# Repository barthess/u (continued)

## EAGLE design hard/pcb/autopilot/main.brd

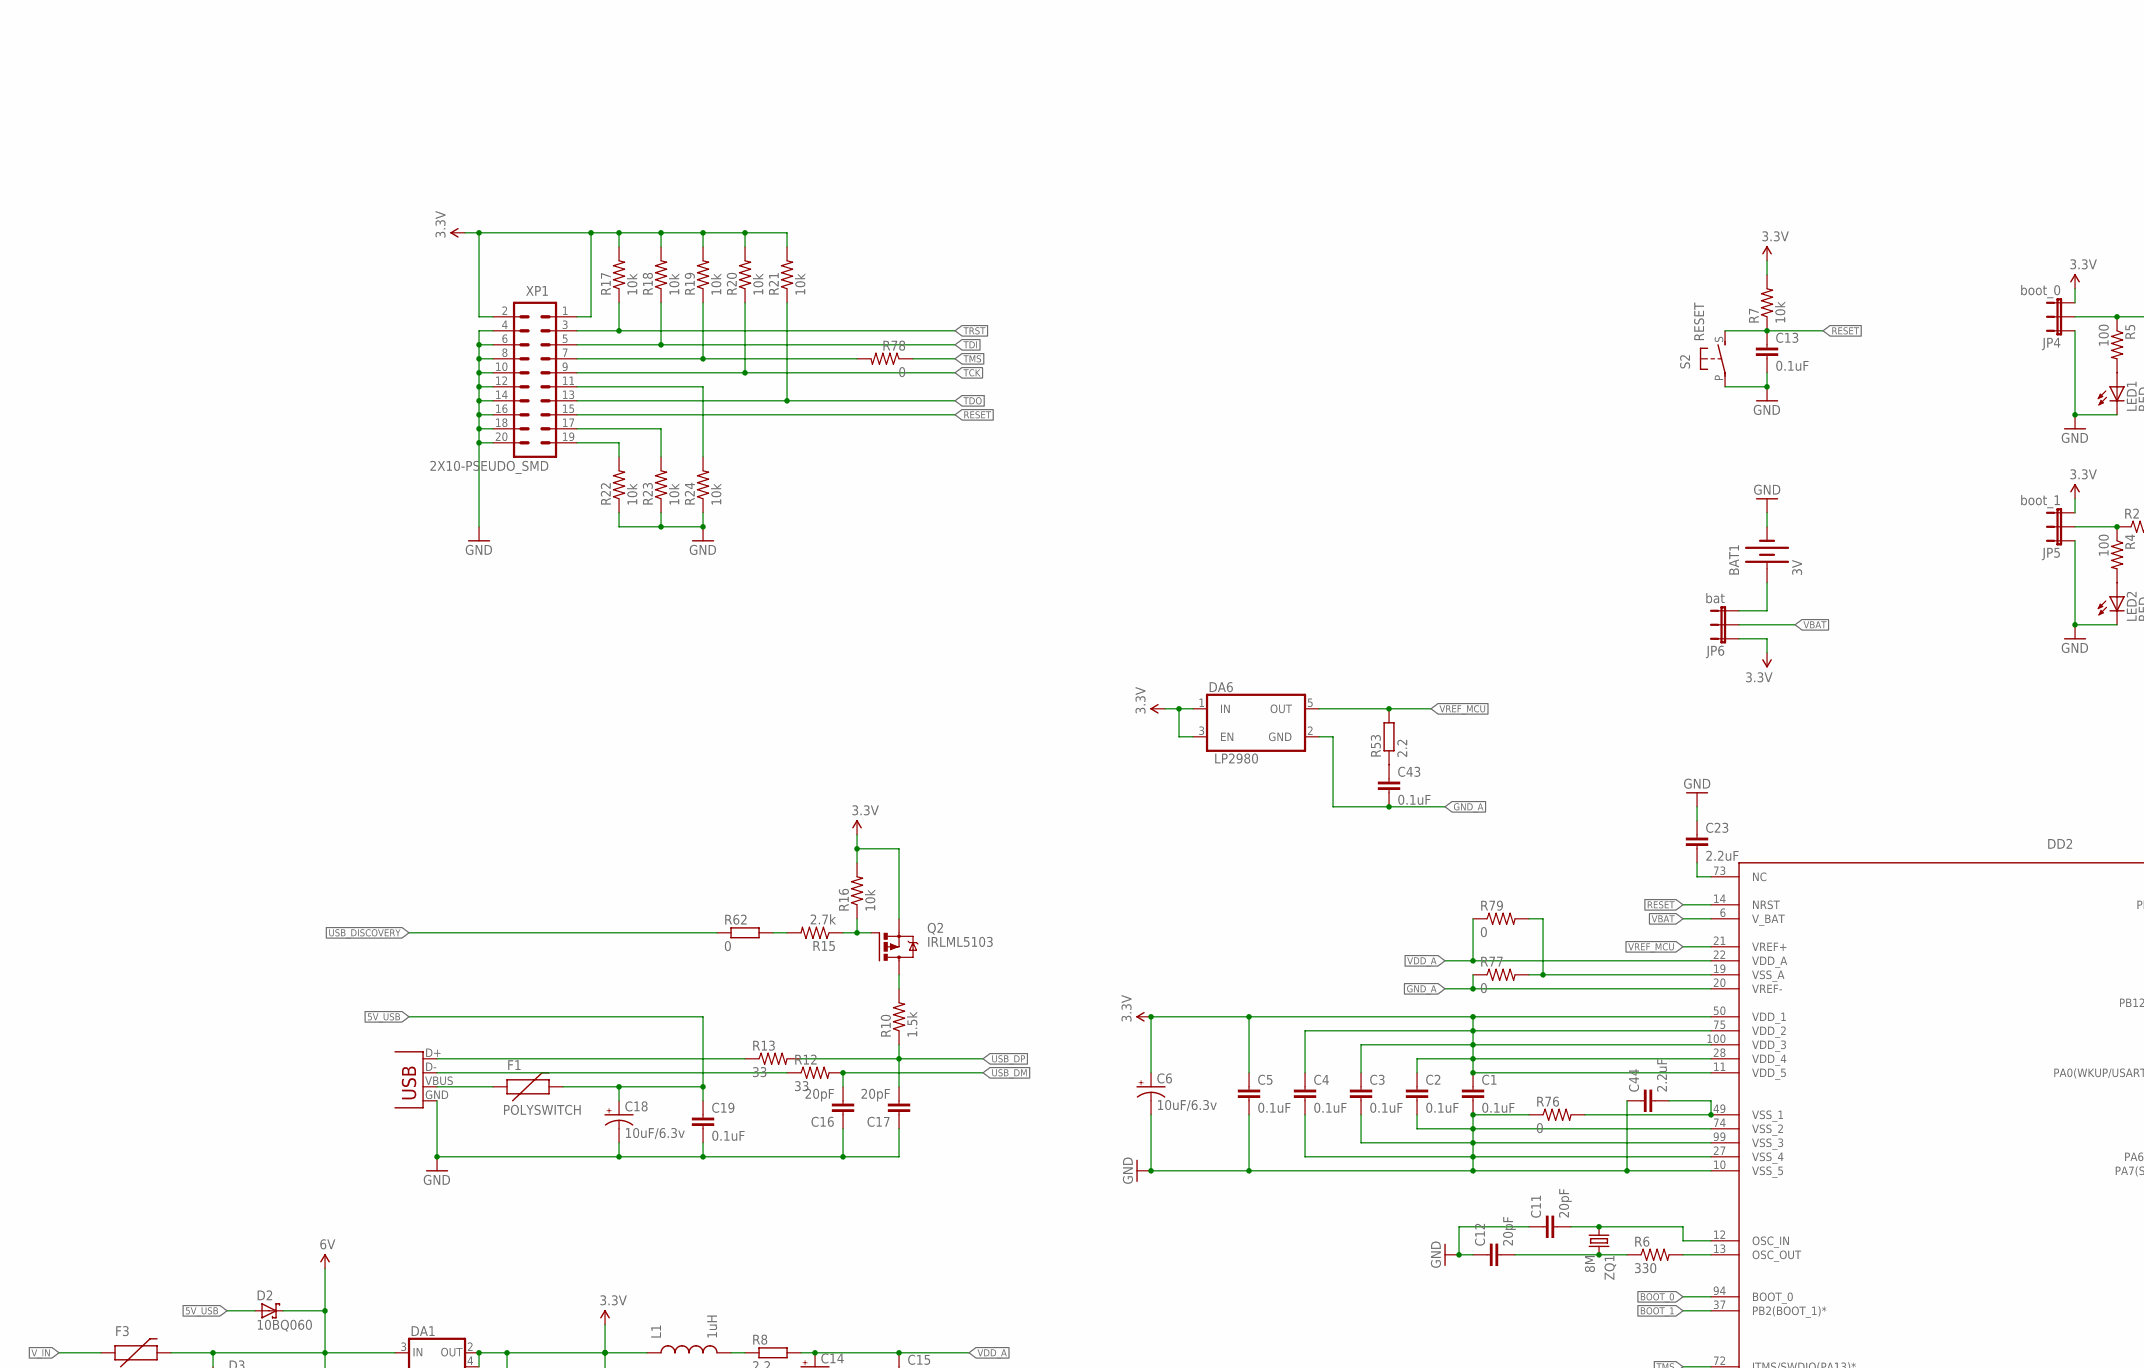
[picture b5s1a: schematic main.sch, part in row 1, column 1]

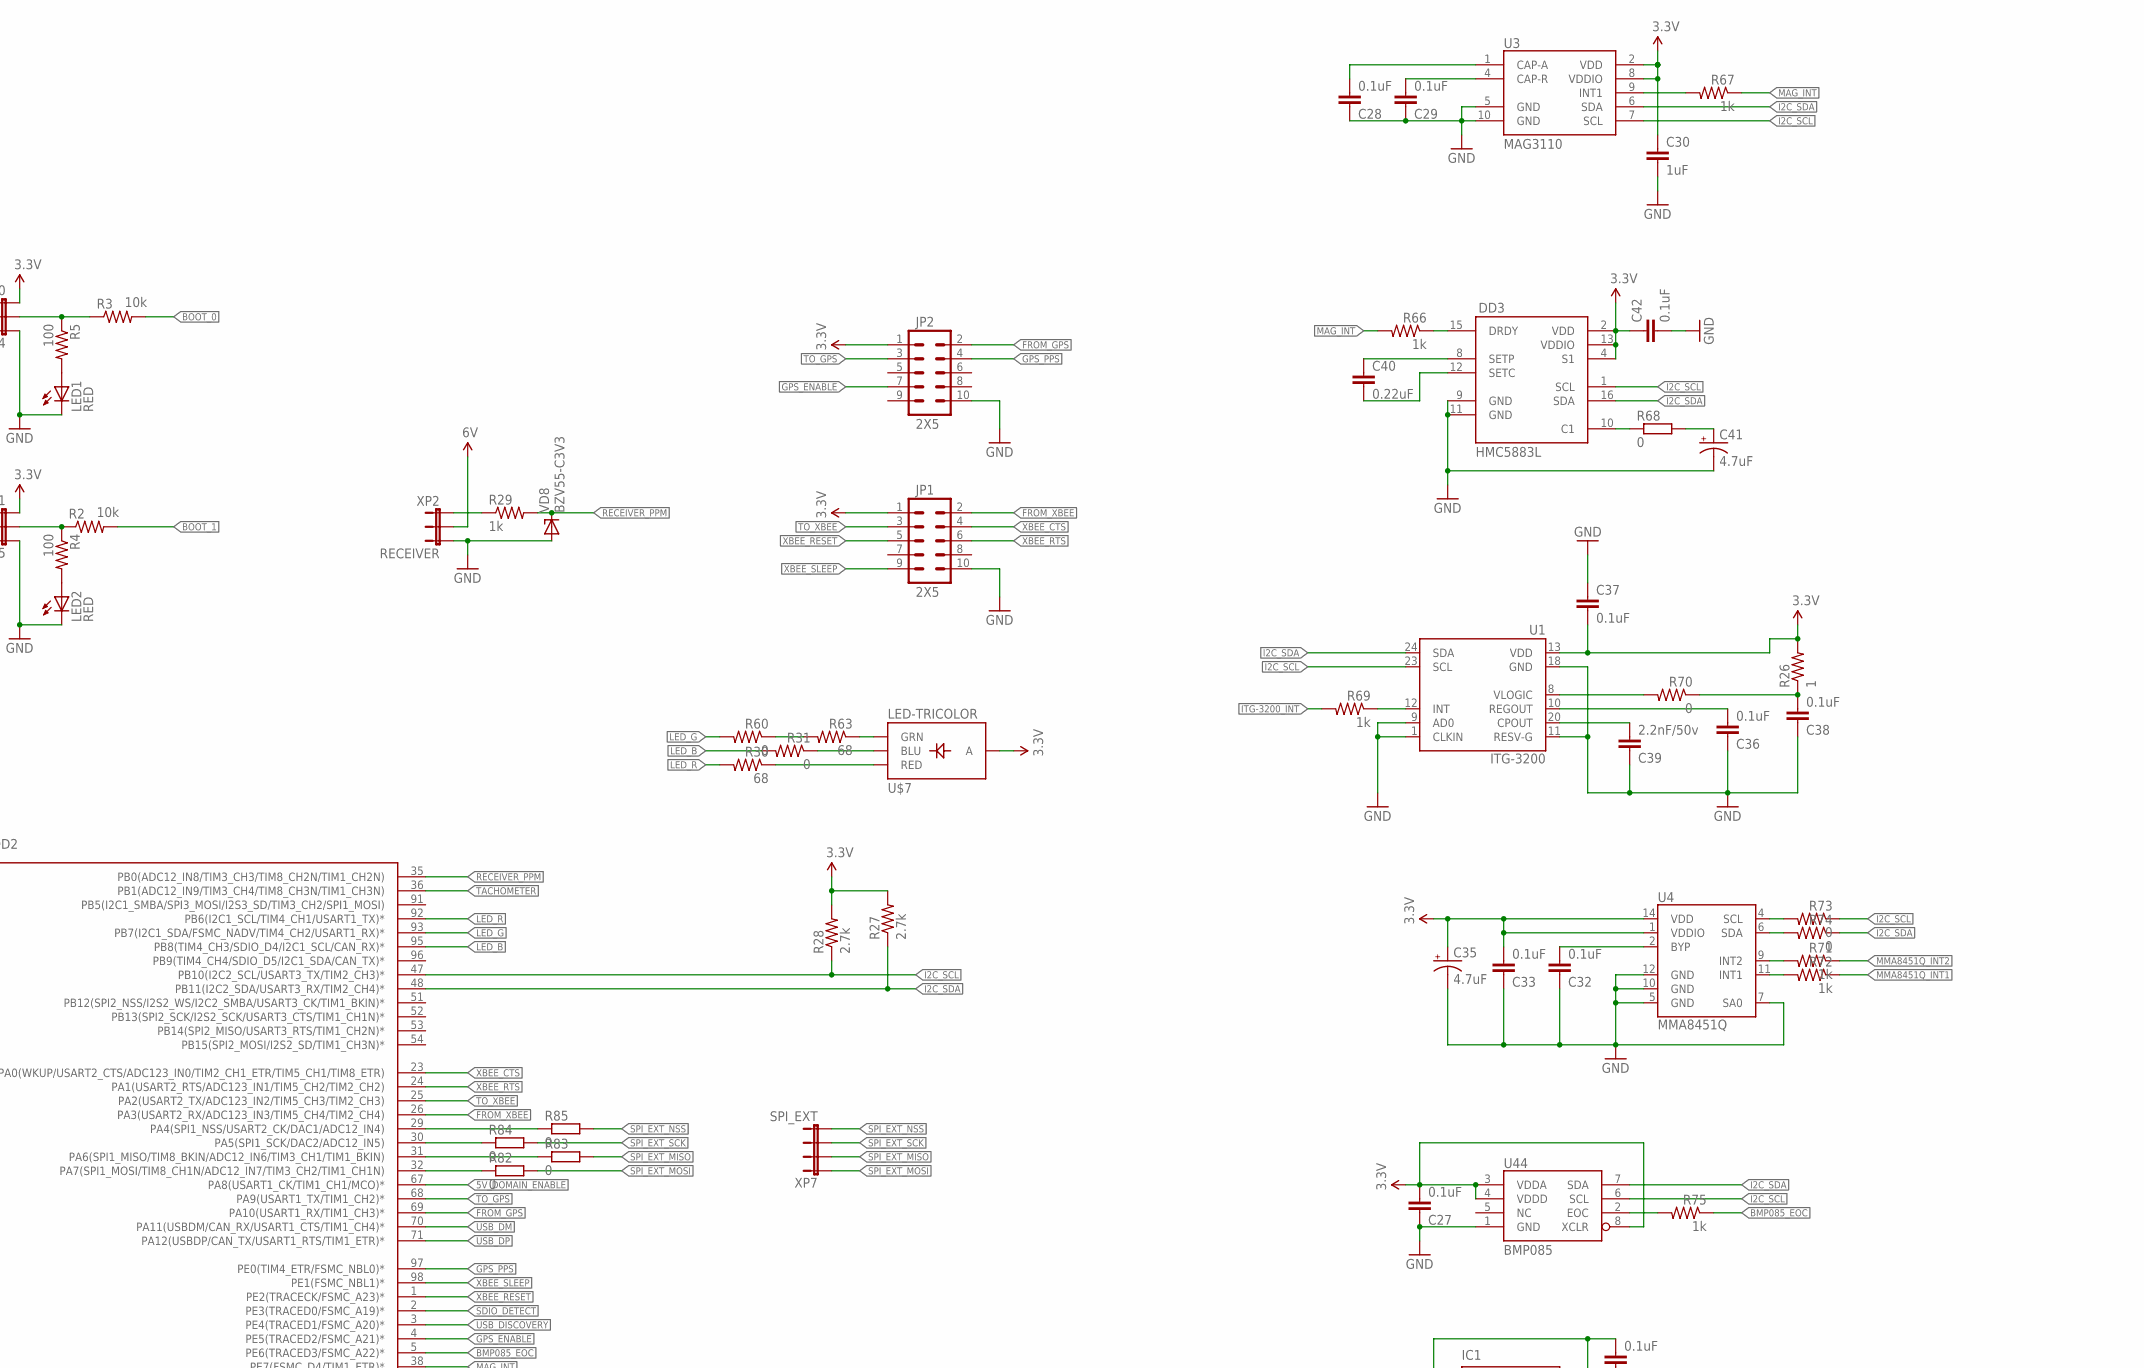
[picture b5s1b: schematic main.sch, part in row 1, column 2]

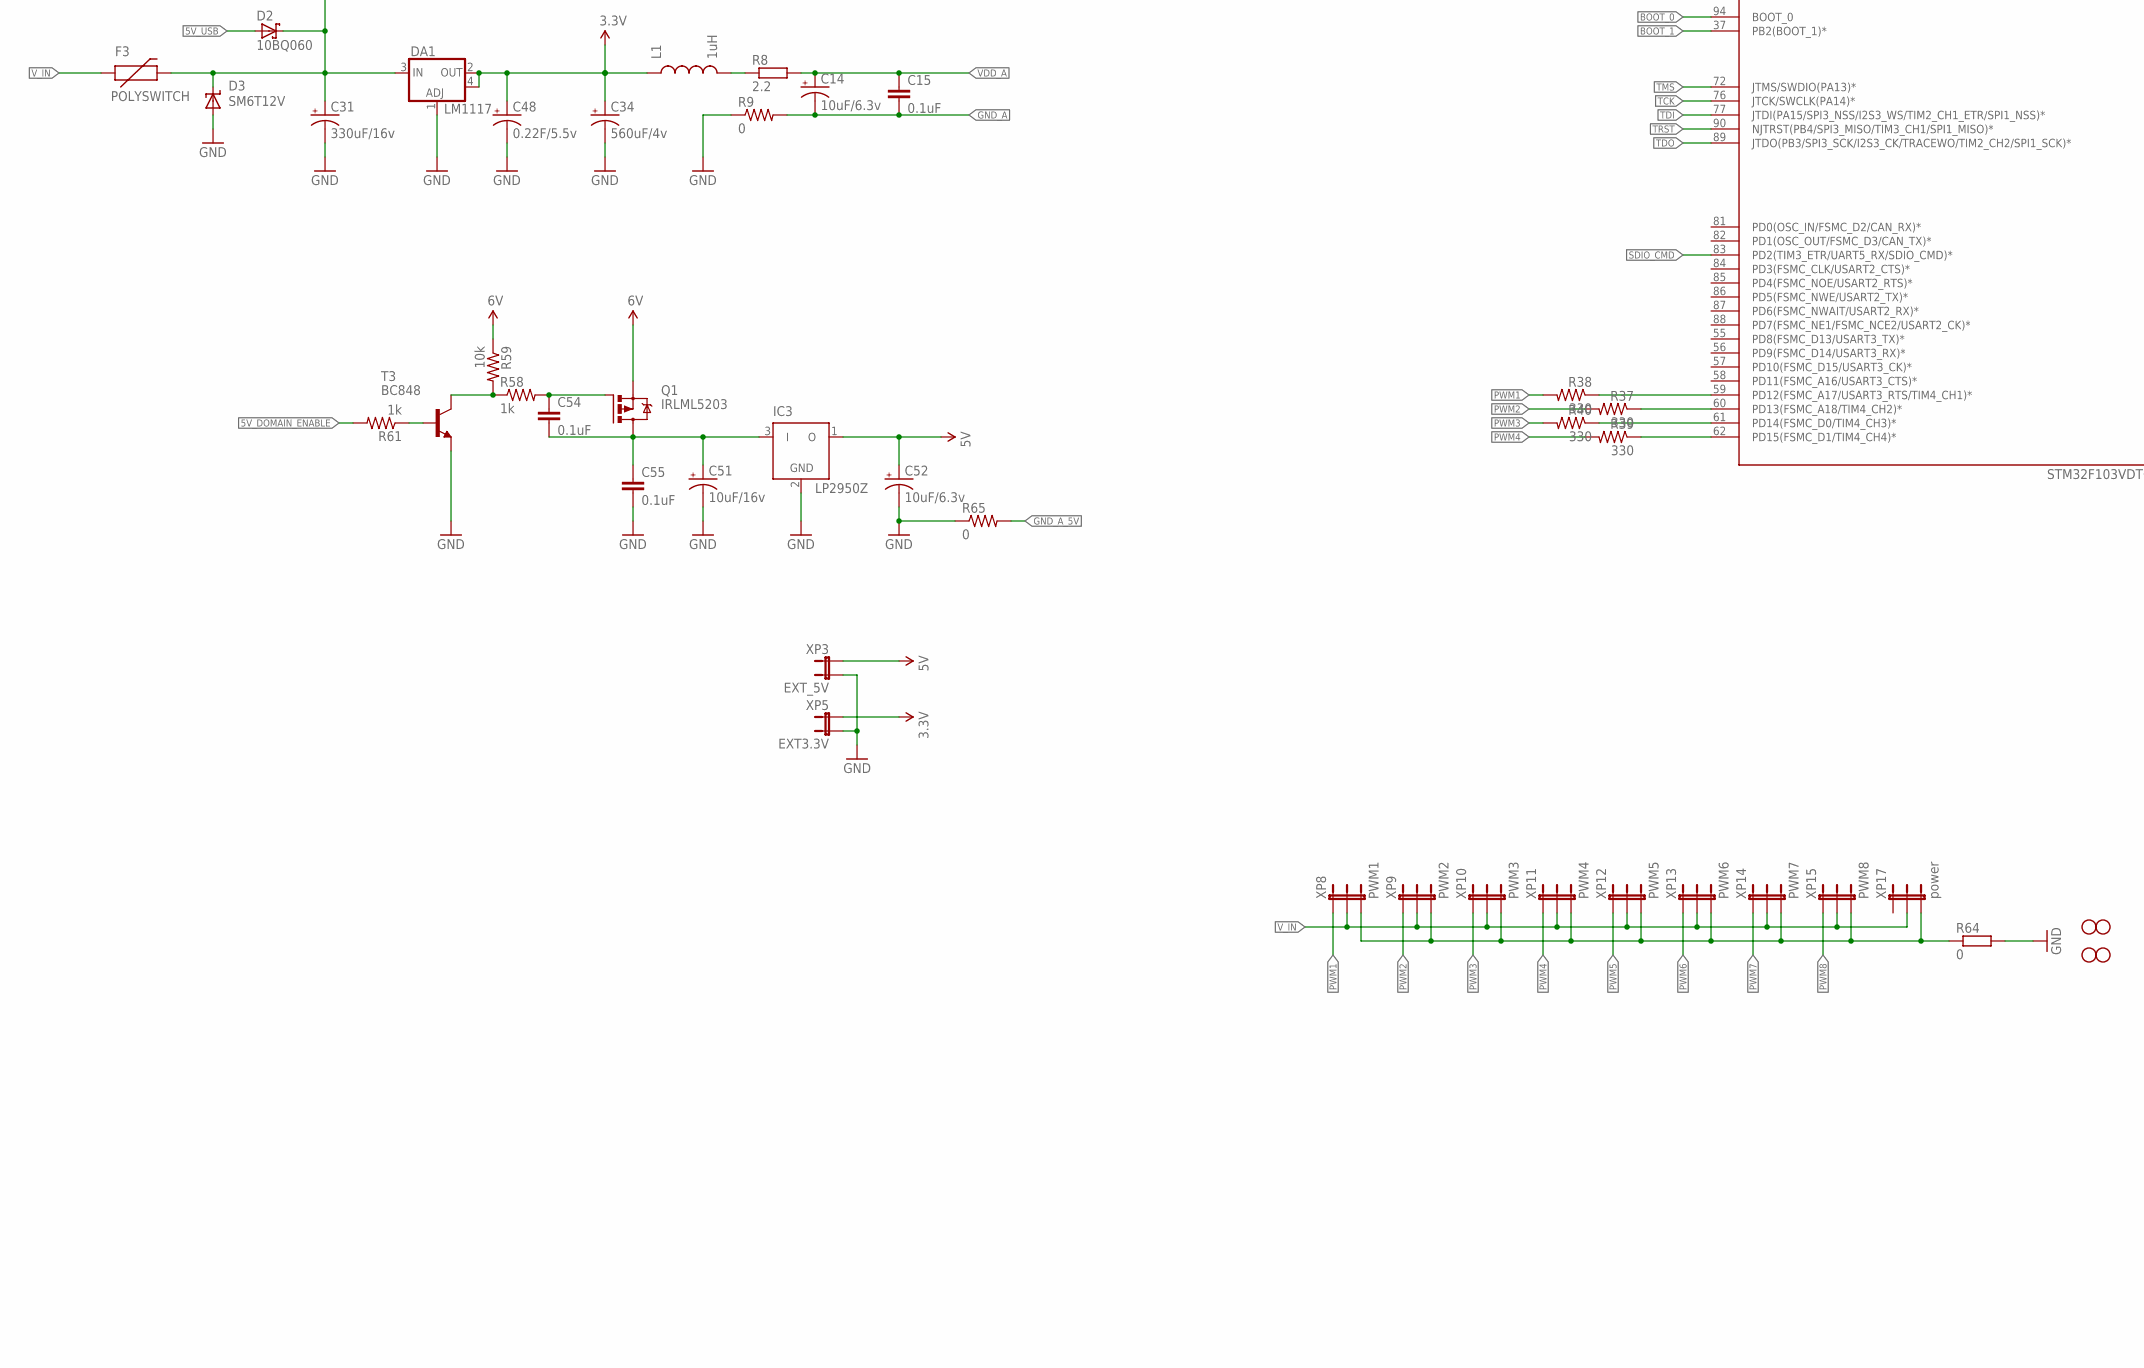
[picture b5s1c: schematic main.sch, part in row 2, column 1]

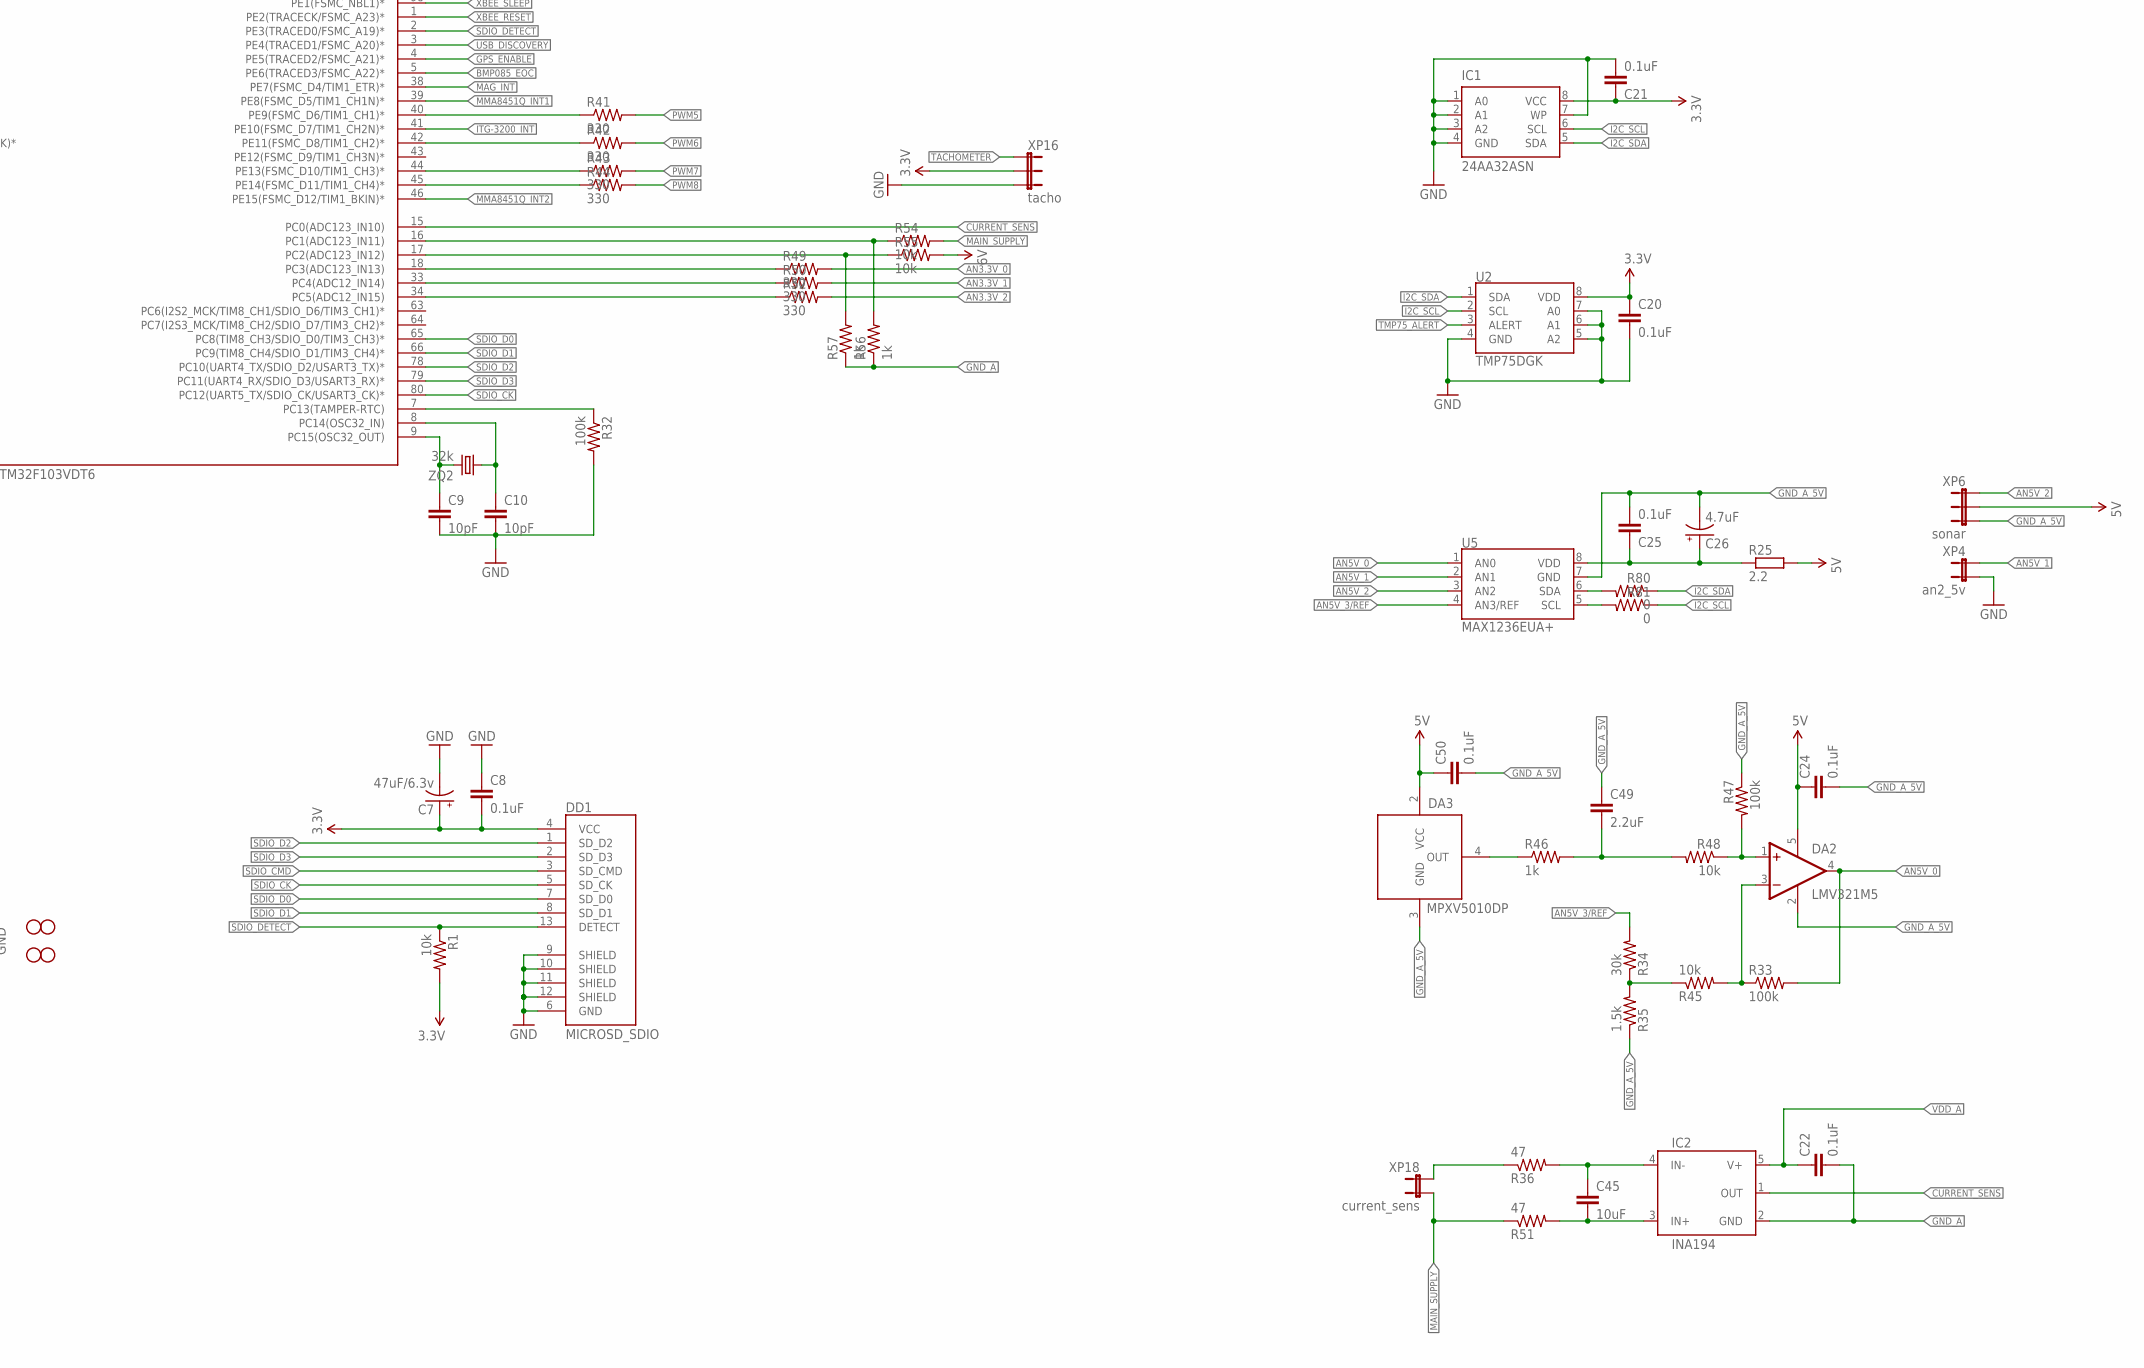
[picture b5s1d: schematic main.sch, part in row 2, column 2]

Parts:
BAT1: 3V; BATTCOM_20MM_PTH
C1, C2, C3, C4, C5, C8, C13, C15, C19, C20, C21, C22, C24, C25, C27, C28, C29, C32, C33, C36, C37, C38, C42, C43, C50, C54, C55: 0.1uF; 0805
C6, C14, C18, C52: 10uF/6.3v; EIA3216-KIT
C7: 47uF/6.3v; EIA3216-KIT
C9, C10: 10pF; 0805
C11, C12, C16, C17: 20pF; 0805
C23, C44: 2.2uF; 0805
C26, C35, C41: 4.7uF; EIA3216-KIT
C30: 1uF; 0805
C31: 330uF/16v; CPOL-RADIAL-1000UF-25V
C34: 560uF/4v; E3,5-8
C39: 2.2nF/50v; 0805
C40: 0.22uF; 0805
C45: 10uF; 1206
C48: 0.22F/5.5v; CAP-IONISTOR-5MM
C49: 2.2uF; C1206
C51: 10uF/16v; EIA3216-KIT
D2: 10BQ060; SMB
D3: SM6T12V; SMBJ
DA1: LM1117; SOT223
DA2: LMV321M5; SOT23-5
DA3: MPXV5010DP; 482
DA6: LP2980; SOT23-5
DD1: MICROSD_SDIO; MICROSD
DD2: STM32F103VDT6; TQFP100
DD3: HMC5883L; 16LPCC
F1, F3: POLYSWITCH; 1812
IC1: 24AA32ASN; SO-08
IC2: INA194; SOT23-5
IC3: LP2950Z; TO92
JP1, JP2: 2X5; 2X5-PSEUDOSMD
JP3, JP7, JP8, JP9: STAND-OFFTIGHT; STAND-OFF-TIGHT
JP4: boot_0; 1X03
JP5: boot_1; 1X03
JP6: bat; 1X03
L1: 1uH; 1210
LED1, LED2: RED; LED-0805
Q1: IRLML5203; MICRO3
Q2: IRLML5103; MICRO3; PARTNO *
R1, R2, R3, R7, R16, R17, R18, R19, R20, R21, R22, R23, R24, R45, R48, R54, R55, R59: 10k; 0805
R4, R5: 100; 0805
R6, R37, R38, R39, R40, R41, R42, R43, R44, R49, R50, R52: 330; 0805
R8, R25, R53: 2.2; R1206
R9, R31, R60, R65, R70, R73, R74, R76, R77, R78, R79, R80, R81: 0; 0805
R10, R35: 1.5k; 0805
R12, R13: 33; 0805
R15, R27, R28: 2.7k; 0805
R26: 1; 0805
R29, R46, R56, R57, R58, R61, R66, R67, R69, R71, R72, R75: 1k; 0805
R30, R63: 68; 0805
R32, R33, R47: 100k; 0805
R34: 30k; 0805
R36, R51: 47; 0805
R62, R64, R68, R82, R83, R84, R85: 0; R1206
S2: RESET; BUTTON_6X3.5
T3: BC848; SOT23
U1: ITG-3200; QFN-24
U2: TMP75DGK; MSOP8
U3: MAG3110; DFN-10
U4: MMA8451Q; QFN-16_0.5MM
U5: MAX1236EUA+; MSOP8
U44: BMP085
U$7: LED-TRICOLOR; LED-TRICOLOR-SMD
VD8: BZV55-C3V3; SOD80C
X1: USB-SMD-NS; USB-MINIB-NOSTOP
XP1: 2X10-PSEUDO_SMD; 2X10-PSEUDOSMD
XP2: RECEIVER; 1X03
XP3: EXT_5V; 1X02
XP4: an2_5v; 1X02
XP5: EXT3.3V; 1X02
XP6: sonar; 1X03
XP7: SPI_EXT; 1X4-PSEUDOSMD
XP8: PWM1; 1X03
XP9: PWM2; 1X03
XP10: PWM3; 1X03
XP11: PWM4; 1X03
XP12: PWM5; 1X03
XP13: PWM6; 1X03
XP14: PWM7; 1X03
XP15: PWM8; 1X03
XP16: tacho; 1X03
XP17: power; 1X03
XP18: current_sens; 1X02
ZQ1: 8M; HC49U-V
ZQ2: 32k; TC38H

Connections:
3.3V: C1.1, C2.1, C3.1, C4.1, C5.1, C6.A (+), C7.A (+), C8.2, C20.1, C21.1, C27.2, C30.1, C33.2, C34.+, C35.A (+), C37.2, C42.1, C48.1 (+), DA1.2 (OUT), DA1.4 (OUT), DA6.1 (IN), DA6.3 (EN), DD1.4 (VCC), DD2.11 (VDD_5), DD2.28 (VDD_4), DD2.50 (VDD_1), DD2.75 (VDD_2), DD2.100 (VDD_3), DD3.2 (VDD), DD3.4 (S1), DD3.13 (VDDIO), IC1.8 (VCC), JP1.1, JP2.1, JP4.3, JP5.3, JP6.1, L1.1, Q2.2 (S), R1.2, R7.2, R16.2, R17.2, R18.2, R19.2, R20.2, R21.2, R26.2, R27.2, R28.2, U1.13 (VDD), U2.8 (VDD), U3.2 (VDD), U3.8 (VDDIO), U4.1 (VDDIO), U4.14 (VDD), U44.3 (VDDA), U44.4 (VDDD), U44.8 (XCLR), U$7.A, XP1.1, XP1.2, XP5.1, XP16.2
5V: C24.1, C50.1, C52.A (+), DA2.5 (V+), DA3.2 (VCC), IC3.1 (O), R25.2, XP3.1, XP6.2
5V_DOMAIN_ENABLE: DD2.67 (PA8(USART1_CK/TIM1_CH1/MCO)*), R61.2
5V_USB: C18.A (+), C19.1, D2.A, F1.2
6V: C31.1 (+), D2.C, D3.C, DA1.3 (IN), F3.2, Q1.2 (S), R55.2, R59.1, XP2.2
AN3.3V_0: R49.2
AN3.3V_1: R50.2
AN3.3V_2: R52.2
AN5V_0: DA2.4 (OUT), R33.2, U5.1 (AN0)
AN5V_1: U5.2 (AN1), XP4.1
AN5V_2: U5.3 (AN2), XP6.1
AN5V_3/REF: R34.2, U5.4 (AN3/REF)
BMP085_EOC: DD2.5 (PE6(TRACED3/FSMC_A22)*), R75.1
BOOT_0: DD2.94 (BOOT_0), R3.2
BOOT_1: DD2.37 (PB2(BOOT_1)*), R2.2
CURRENT_SENS: DD2.15 (PC0(ADC123_IN10)), IC2.1 (OUT)
FROM_GPS: DD2.69 (PA10(USART1_RX/TIM1_CH3)*), JP2.2
FROM_XBEE: DD2.26 (PA3(USART2_RX/ADC123_IN3/TIM5_CH4/TIM2_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), JP1.2
GND: BAT1.2 (-), C1.2, C2.2, C3.2, C4.2, C5.2, C6.C (-), C7.C (-), C8.1, C9.2, C10.2, C11.1, C12.1, C13.2, C16.1, C17.1, C18.C (-), C19.2, C20.2, C21.2, C23.1, C27.1, C28.1, C29.1, C30.2, C31.2 (-), C32.1, C33.1, C34.-, C35.C (-), C36.1, C37.1, C38.1, C39.1, C41.C (-), C42.2, C44.1, C48.2 (-), C51.C (-), C52.C (-), C55.2, D3.A, DA1.1 (ADJ), DD1.6 (GND), DD1.9 (SHIELD), DD1.10 (SHIELD), DD1.11 (SHIELD), DD1.12 (SHIELD), DD2.10 (VSS_5), DD2.27 (VSS_4), DD2.74 (VSS_2), DD2.99 (VSS_3), DD3.9 (GND), DD3.11 (GND), IC1.1 (A0), IC1.2 (A1), IC1.3 (A2), IC1.4 (GND), IC1.7 (WP), IC3.2 (GND), JP1.10, JP2.10, JP4.1, JP5.1, LED1.C, LED2.C, R9.1, R22.1, R23.1, R24.1, R32.2, R64.2, R65.1, R76.1, S2.P, T3.2 (E), U1.1 (CLKIN), U1.9 (AD0), U1.11 (RESV-G), U1.18 (GND), U2.4 (GND), U2.5 (A2), U2.6 (A1), U2.7 (A0), U3.5 (GND), U3.10 (GND), U4.5 (GND), U4.7 (SA0), U4.10 (GND), U4.12 (GND), U44.1 (GND), VD8.A, X1.GND, XP1.4, XP1.6, XP1.8, XP1.10, XP1.12, XP1.14, XP1.16, XP1.18, XP1.20, XP2.3, XP3.2, XP4.2, XP5.2, XP16.3
GND_A: C14.C (-), C15.2, C22.2, C43.2, DA6.2 (GND), DD2.20 (VREF-), IC2.2 (GND), R9.2, R56.1, R57.1, R77.1
GND_A_5V: C24.2, C25.2, C26.C (-), C49.1, C50.2, DA2.2 (V-), DA3.3 (GND), R35.1, R47.1, R65.2, U5.7 (GND), XP6.3
GPS_ENABLE: DD2.4 (PE5(TRACED2/FSMC_A21)*), JP2.7
GPS_PPS: DD2.97 (PE0(TIM4_ETR/FSMC_NBL0)*), JP2.4
I2C_SCL: DD2.47 (PB10(I2C2_SCL/USART3_TX/TIM2_CH3)*), DD3.1 (SCL), IC1.6 (SCL), R28.1, R73.1, R81.1, U1.23 (SCL), U2.2 (SCL), U3.7 (SCL), U44.6 (SCL)
I2C_SDA: DD2.48 (PB11(I2C2_SDA/USART3_RX/TIM2_CH4)*), DD3.16 (SDA), IC1.5 (SDA), R27.1, R74.1, R80.1, U1.24 (SDA), U2.1 (SDA), U3.6 (SDA), U44.7 (SDA)
ITG-3200_INT: DD2.41 (PE10(FSMC_D7/TIM1_CH2N)*), R69.2
LED_B: DD2.95 (PB8(TIM4_CH3/SDIO_D4/I2C1_SCL/CAN_RX)*), R31.2
LED_G: DD2.93 (PB7(I2C1_SDA/FSMC_NADV/TIM4_CH2/USART1_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), R60.2
LED_R: DD2.92 (PB6(I2C1_SCL/TIM4_CH1/USART1_TX)*), R30.2
MAG_INT: DD2.38 (PE7(FSMC_D4/TIM1_ETR)*), R66.2, R67.1
MAIN_SUPPLY: R51.1, R54.2, XP18.2
MMA8451Q_INT1: DD2.39 (PE8(FSMC_D5/TIM1_CH1N)*), R72.1
MMA8451Q_INT2: DD2.46 (PE15(FSMC_D12/TIM1_BKIN)*), R71.1
unnamed: C9.1, DD2.9 (PC15(OSC32_OUT)), ZQ2.2
unnamed: LED2.A, R4.2
unnamed: JP5.2, R2.1, R4.1
unnamed: LED1.A, R5.2
unnamed: JP4.2, R3.1, R5.1
unnamed: C10.1, DD2.8 (PC14(OSC32_IN)), ZQ2.1
unnamed: DD2.13 (OSC_OUT), R6.2
unnamed: C12.2, R6.1, ZQ1.2
unnamed: C11.2, DD2.12 (OSC_IN), ZQ1.1
unnamed: R12.1, X1.D-
unnamed: BAT1.1 (+), JP6.3
unnamed: L1.2, R8.1
unnamed: R13.1, X1.D+
unnamed: Q2.3 (D), R10.2
unnamed: Q2.1 (G), R15.1, R16.1
unnamed: R22.2, XP1.19
unnamed: R23.2, XP1.17
unnamed: R24.2, XP1.11
unnamed: C45.1, IC2.4 (IN-), R36.2
unnamed: C25.1, C26.A (+), R25.1, U5.8 (VDD)
unnamed: C32.2, U4.2 (BYP)
unnamed: C36.2, U1.10 (REGOUT)
unnamed: C29.2, U3.4 (CAP-R)
unnamed: C38.2, R26.1, R70.1
unnamed: C28.2, U3.1 (CAP-A)
unnamed: C40.1, DD3.8 (SETP)
unnamed: C40.2, DD3.12 (SETC)
unnamed: F1.1, X1.VBUS
unnamed: C39.2, U1.20 (CPOUT)
unnamed: C41.A (+), R68.2
unnamed: R29.1, XP2.1
unnamed: R63.1, U$7.G (GRN)
unnamed: DD2.7 (PC13(TAMPER-RTC)), R32.1
unnamed: C49.2, R46.2, R48.2
unnamed: DD2.32 (PA7(SPI1_MOSI/TIM8_CH1N/ADC12_IN7/TIM3_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), R82.1
unnamed: C45.2, IC2.3 (IN+), R51.2
unnamed: C43.1, R53.1
unnamed: R36.1, XP18.1
unnamed: DD2.62 (PD15(FSMC_D1/TIM4_CH4)*), R39.1
unnamed: DD2.61 (PD14(FSMC_D0/TIM4_CH3)*), R40.1
unnamed: DD2.60 (PD13(FSMC_A18/TIM4_CH2)*), R37.1
unnamed: DD2.59 (PD12(FSMC_A17/USART3_RTS/TIM4_CH1)*), R38.1
unnamed: DA3.4 (OUT), R46.1
unnamed: DD2.34 (PC5(ADC12_IN15)), R52.1
unnamed: DA2.3 (-IN), R33.1, R45.2
unnamed: DA2.1 (+IN), R47.2, R48.1
unnamed: R34.1, R35.2, R45.1
unnamed: DD2.33 (PC4(ADC12_IN14)), R50.1
unnamed: DD2.18 (PC3(ADC123_IN13)), R49.1
unnamed: DD2.31 (PA6(SPI1_MISO/TIM8_BKIN/ADC12_IN6/TIM3_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), R83.1
unnamed: DD2.16 (PC1(ADC123_IN11)), R54.1, R56.2
unnamed: C54.1, Q1.1 (G), R58.2
unnamed: DD2.17 (PC2(ADC123_IN12)), R55.1, R57.2
unnamed: C51.A (+), C54.2, C55.1, IC3.3 (I), Q1.3 (D)
unnamed: R31.1, U$7.B (BLU)
unnamed: R30.1, U$7.R (RED)
unnamed: DD2.30 (PA5(SPI1_SCK/DAC2/ADC12_IN5)), R84.1
unnamed: R61.1, T3.1 (B)
unnamed: DD2.29 (PA4(SPI1_NSS/USART2_CK/DAC1/ADC12_IN4)), R85.1
unnamed: DD2.45 (PE14(FSMC_D11/TIM1_CH4)*), R44.1
unnamed: DD2.44 (PE13(FSMC_D10/TIM1_CH3)*), R43.1
unnamed: DD2.42 (PE11(FSMC_D8/TIM1_CH2)*), R42.1
unnamed: DD2.40 (PE9(FSMC_D6/TIM1_CH1)*), R41.1
unnamed: R67.2, U3.9 (INT1)
unnamed: DD3.15 (DRDY), R66.1
unnamed: DD3.10 (C1), R68.1
unnamed: R69.1, U1.12 (INT)
unnamed: R70.2, U1.8 (VLOGIC)
unnamed: R71.2, U4.9 (INT2)
unnamed: R72.2, U4.11 (INT1)
unnamed: R74.2, U4.6 (SDA)
unnamed: R73.2, U4.4 (SCL)
unnamed: R75.2, U44.2 (EOC)
unnamed: R15.2, R62.2
unnamed: R60.1, R63.2
unnamed: R19.1, R78.2, XP1.7
unnamed: R64.1, XP8.3, XP9.3, XP10.3, XP11.3, XP12.3, XP13.3, XP14.3, XP15.3, XP17.3
unnamed: R80.2, U5.6 (SDA)
unnamed: R81.2, U5.5 (SCL)
unnamed: C23.2, DD2.73 (NC)
unnamed: C44.2, DD2.49 (VSS_1), R76.2
unnamed: DD2.19 (VSS_A), R77.2, R79.2
NET$1: R58.1, R59.2, T3.3 (C)
PWM1: R38.2, XP8.1
PWM2: R37.2, XP9.1
PWM3: R40.2, XP10.1
PWM4: R39.2, XP11.1
PWM5: R41.2, XP12.1
PWM6: R42.2, XP13.1
PWM7: R43.2, XP14.1
PWM8: R44.2, XP15.1
RECEIVER_PPM: DD2.35 (PB0(ADC12_IN8/TIM3_CH3/TIM8_CH2N/TIM1_C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), R29.2, VD8.C
RESET: C13.1, DD2.14 (NRST), R7.1, S2.S, XP1.15
SDIO_CK: DD1.5 (SD_CK), DD2.80 (PC12(UART5_TX/SDIO_CK/USART3_CK)*)
SDIO_CMD: DD1.3 (SD_CMD), DD2.83 (PD2(TIM3_ETR/UART5_RX/SDIO_CMD)*)
SDIO_D0: DD1.7 (SD_D0), DD2.65 (PC8(TIM8_CH3/SDIO_D0/TIM3_CH3)*)
SDIO_D1: DD1.8 (SD_D1), DD2.66 (PC9(TIM8_CH4/SDIO_D1/TIM3_CH4)*)
SDIO_D2: DD1.1 (SD_D2), DD2.78 (PC10(UART4_TX/SDIO_D2/USART3_TX)*)
SDIO_D3: DD1.2 (SD_D3), DD2.79 (PC11(UART4_RX/SDIO_D3/USART3_RX)*)
SDIO_DETECT: DD1.13 (DETECT), DD2.2 (PE3(TRACED0/FSMC_A19)*), R1.1
SPI_EXT_MISO: R83.2, XP7.2
SPI_EXT_MOSI: R82.2, XP7.1
SPI_EXT_NSS: R85.2, XP7.4
SPI_EXT_SCK: R84.2, XP7.3
TACHOMETER: DD2.36 (PB1(ADC12_IN9/TIM3_CH4/TIM8_CH3N/TIM1_C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), XP16.1
TCK: DD2.76 (JTCK/SWCLK(PA14)*), R20.1, XP1.9
TDI: DD2.77 (JTDI(PA15/SPI3_NSS/I2S3_WS/TIM2_CH1_ETR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), R18.1, XP1.5
TDO: DD2.89 (JTDO(PB3/SPI3_SCK/I2S3_CK/TRACEWO/TIM2_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), R21.1, XP1.13
TMP75_ALERT: U2.3 (ALERT)
TMS: DD2.72 (JTMS/SWDIO(PA13)*), R78.1
TO_GPS: DD2.68 (PA9(USART1_TX/TIM1_CH2)*), JP2.3
TO_XBEE: DD2.25 (PA2(USART2_TX/ADC123_IN2/TIM5_CH3/TIM2_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), JP1.3
TRST: DD2.90 (NJTRST(PB4/SPI3_MISO/TIM3_CH1/SPI1_MISO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), R17.1, XP1.3
USB_DISCOVERY: DD2.3 (PE4(TRACED1/FSMC_A20)*), R62.1
USB_DM: C16.2, DD2.70 (PA11(USBDM/CAN_RX/USART1_CTS/TIM1_CH4)*), R12.2
USB_DP: C17.2, DD2.71 (PA12(USBDP/CAN_TX/USART1_RTS/TIM1_ETR)*), R10.1, R13.2
VBAT: DD2.6 (V_BAT), JP6.2
VDD_A: C14.A (+), C15.1, C22.1, DD2.22 (VDD_A), IC2.5 (V+), R8.2, R79.1
VREF_MCU: DA6.5 (OUT), DD2.21 (VREF+), R53.2
V_IN: F3.1, XP8.2, XP9.2, XP10.2, XP11.2, XP12.2, XP13.2, XP14.2, XP15.2, XP17.2
XBEE_CTS: DD2.23 (PA0(WKUP/USART2_CTS/ADC123_IN0/TIM2_CH1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), JP1.4
XBEE_RESET: DD2.1 (PE2(TRACECK/FSMC_A23)*), JP1.5
XBEE_RTS: DD2.24 (PA1(USART2_RTS/ADC123_IN1/TIM5_CH2/TIM2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), JP1.6
XBEE_SLEEP: DD2.98 (PE1(FSMC_NBL1)*), JP1.9

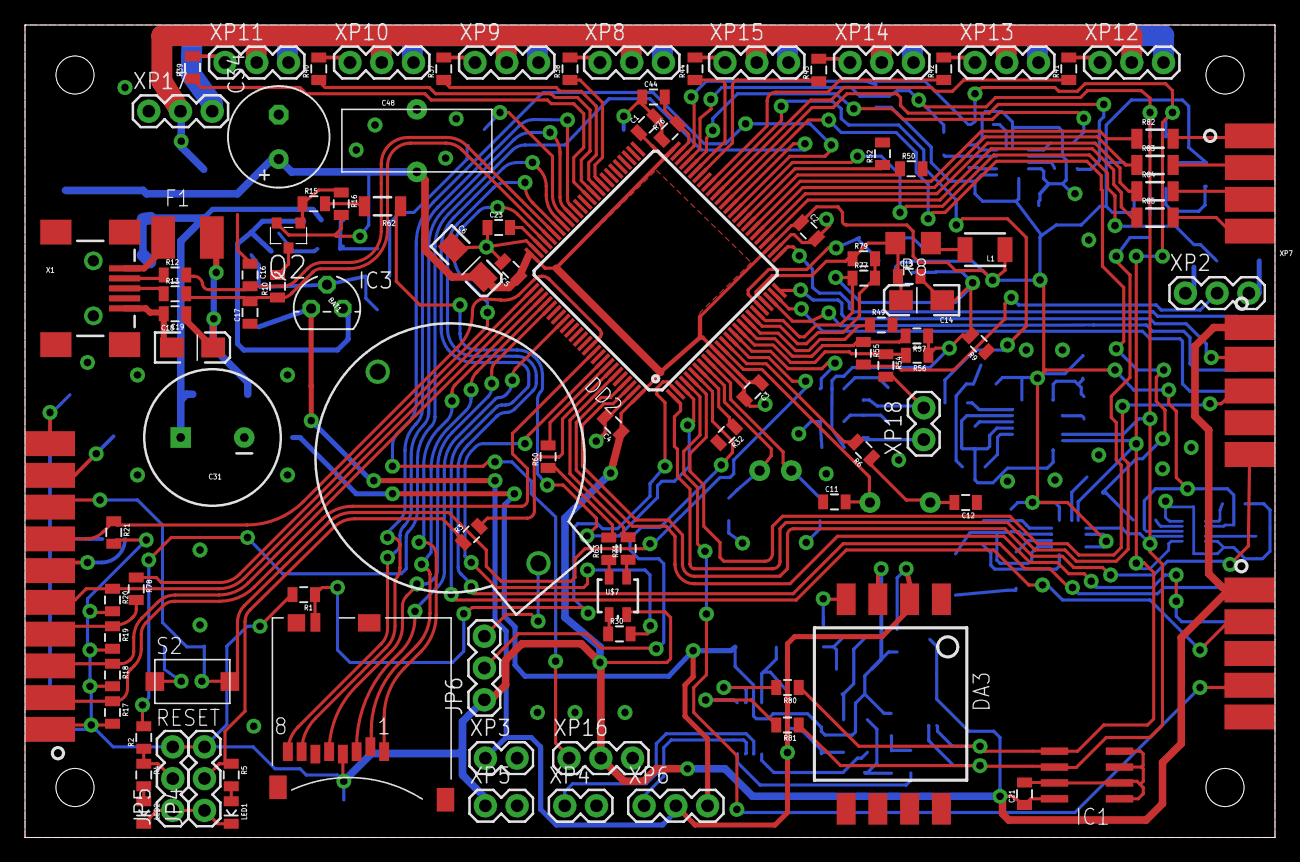
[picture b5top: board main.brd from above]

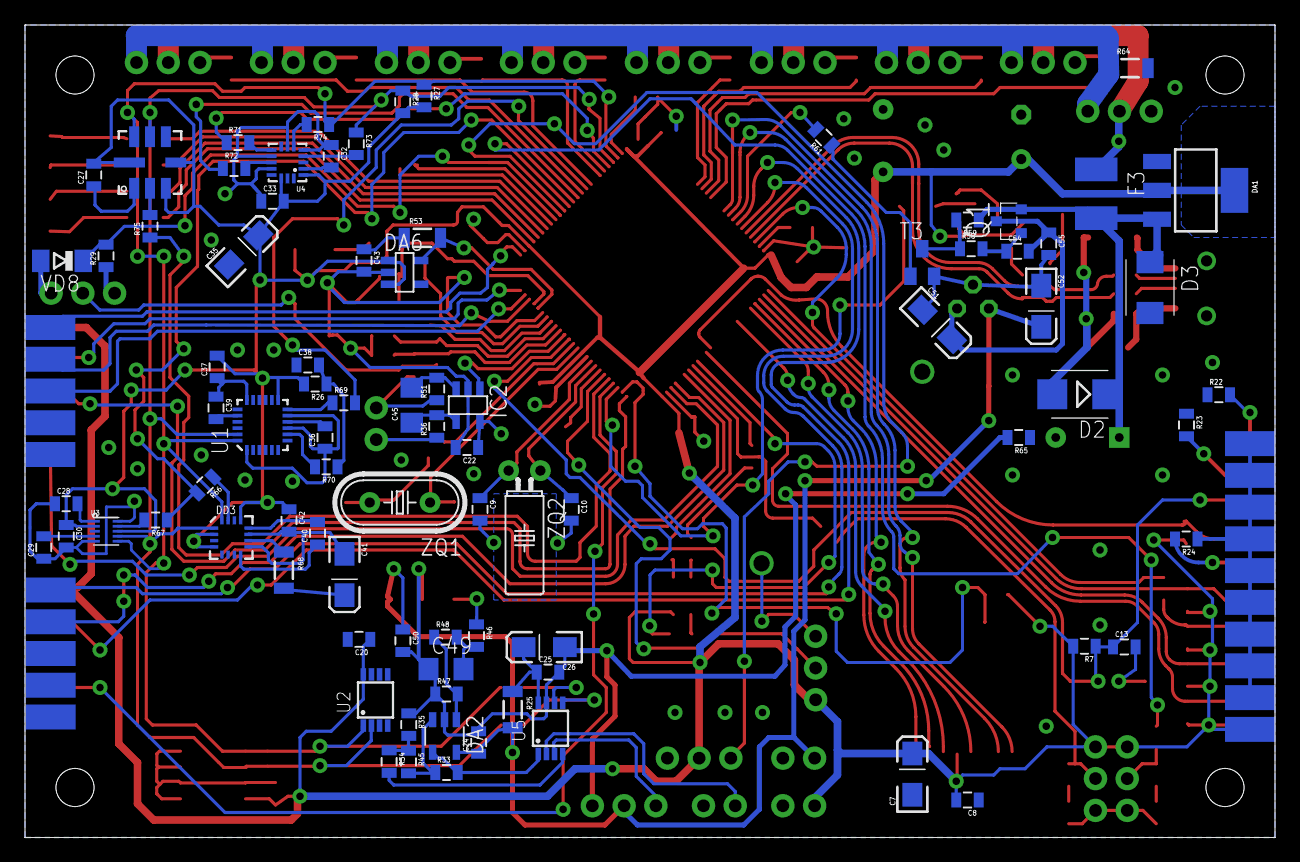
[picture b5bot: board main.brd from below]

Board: 2 copper layers, 100.0 x 65.0 mm, 195 parts (85 on the bottom side), 153 nets.

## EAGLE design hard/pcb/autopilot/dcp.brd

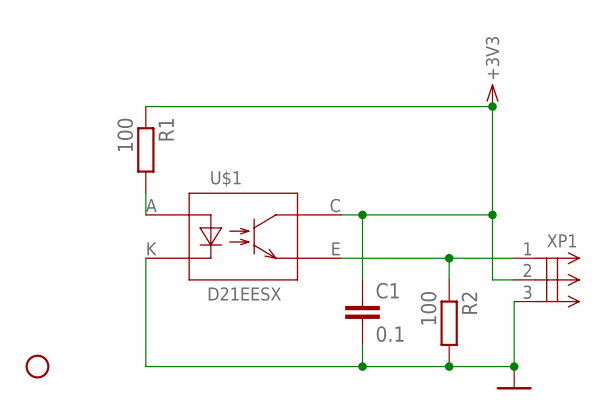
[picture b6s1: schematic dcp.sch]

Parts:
C1: 0.1; 0805
JP1: STAND-OFF-M3
R1, R2: 100; 0805
U$1: D21EESX
XP1: PLD_1X03LONGPAD; PLD_1X03_LONGPAD

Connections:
+3V3: C1.1, R1.1, U$1.C (TC), XP1.2
GND: C1.2, R2.2, U$1.K (DC), XP1.3
unnamed: R2.1, U$1.E (TE), XP1.1
unnamed: R1.2, U$1.A (DA)

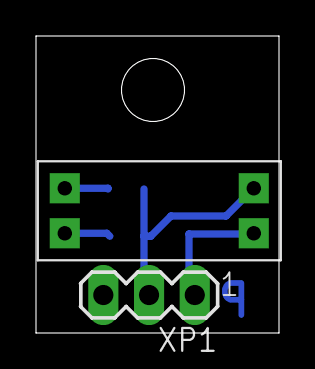
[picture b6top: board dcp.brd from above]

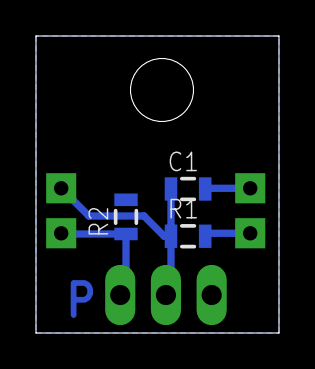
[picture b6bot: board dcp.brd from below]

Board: 2 copper layers, 13.5 x 16.5 mm, 6 parts (3 on the bottom side), 4 nets.
